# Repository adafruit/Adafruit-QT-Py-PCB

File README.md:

## Adafruit QT Py PCB

<a href="http://www.adafruit.com/products/4600"><br/>
Click here to purchase one from the Adafruit shop</a>

PCB files for the Adafruit QT Py.

Format is EagleCAD schematic and board layout
* https://www.adafruit.com/product/4600

### Description

What a cutie pie! Or is it... a QT Py? This diminutive dev board comes with our favorite lil chip, the SAMD21 (as made famous in our GEMMA M0 and Trinket M0 boards).

This time it comes with our favorite connector - the STEMMA QT, a chainable I2C port that can be used with any of our STEMMA QT sensors and accessories.

OLEDs! Inertial Measurment Units! Sensors a-plenty. All plug-and-play thanks to the innovative chainable design: SparkFun Qwiic-compatible STEMMA QT connectors for the I2C bus so you don't even need to solder! Just plug in a compatible cable and attach it to your MCU of choice, and you’re ready to load up some software and measure some light.

Use any SparkFun Qwiic boards! Seeed Grove I2C boards will also work with this adapter cable.

Pinout and shape is Seeed Xiao compatible, with castellated pads so you can solder it flat to a PCB. In addition to the QT connector, we also added an RGB NeoPixel (with controllable power pin to allow for ultra-low-power usage), and a reset button (great for restarting your program, or entering the bootloader)

Runs Arduino like a dream, and can be used for basic CircuitPython projects. For more advanced usage like datalogging or file storage, solder an SOIC SPI flash chip onto the bottom pads,

    Same size, form-factor, and pin-out as Seeed Xiao
    ATSAMD21E18 32-bit Cortex M0+ - 48 MHz 32 bit processor with 256KB Flash and 32 KB RAM
    Native USB supported by every OS - can be used in Arduino or CircuitPython as USB serial console, MIDI, Keyboard/Mouse HID, even a little disk drive for storing Python scripts.
    Can be used with Arduino IDE or CircuitPython
    Built in RGB NeoPixel LED
    11 GPIO pins:
        True analog output on one I/O pin - can be used to play 10-bit quality audio clips in Arduino (CircuitPython does not have storage for audio clips)
        9 x 12-bit analog inputs (SDA/SCL do not have analog inputs)
        1 x Optional AREF on A1
        9 x PWM outputs (A0 is analog out, A1 is not PWM capable)
        Hardware I2C port with STEMMA QT plug-n-play connector
        Hardware UART
        Hardware SPI
        Hardware I2S
        6 x Capacitive Touch with no additional components required
    3.3V regulator with 600mA peak output
    Optional SOIC-8 SPI Flash chip on bottom
    Reset switch for starting your project code over or entering bootloader mode
    USB Type C connector
    Really really small

### License

Adafruit invests time and resources providing this open source design, please support Adafruit and open-source hardware by purchasing products from [Adafruit](https://www.adafruit.com)!

Designed by Limor Fried/Ladyada for Adafruit Industries.

Creative Commons Attribution/Share-Alike, all text above must be included in any redistribution.
See license.txt for additional details.

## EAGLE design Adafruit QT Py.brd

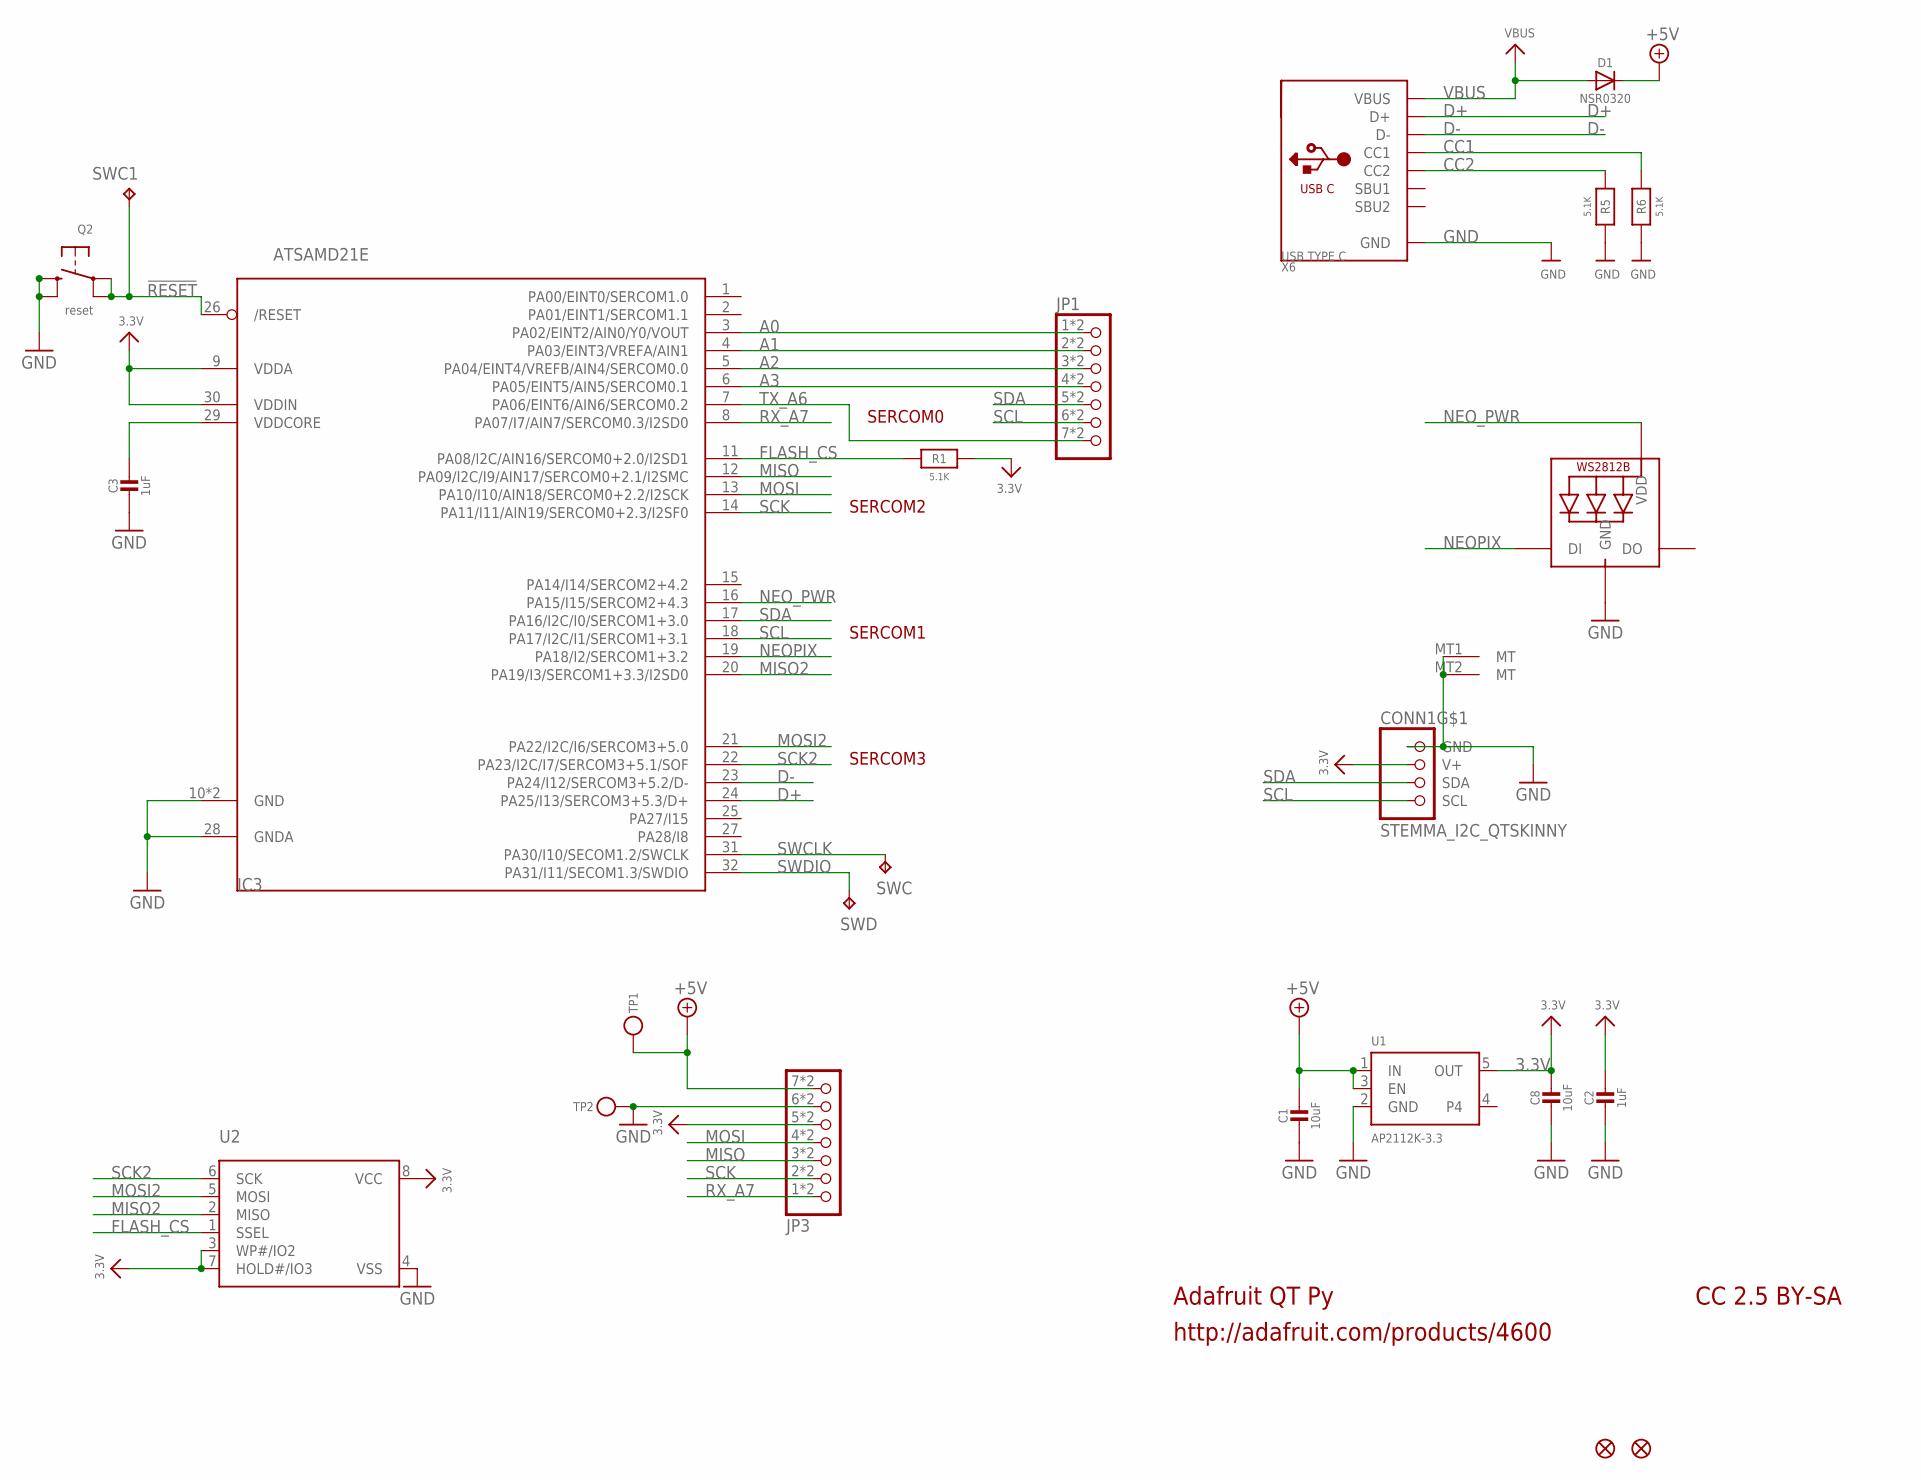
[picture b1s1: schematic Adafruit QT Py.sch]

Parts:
C1, C8: 10uF; _0805MP
C2, C3: 1uF; _0402NO
CONN1: STEMMA_I2C_QTSKINNY; JST_SH4_SKINNY
D1: NSR0320; SOD-323_MINI
IC3: ATSAMD21E; QFN32_5MM
JP1, JP3: HEADER-1X7_CASTEL; 1X07_CASTEL
LED1: WS2812B_SK6805_1515; SK6805_1515
Q2: reset; BTN_KMR2_4.6X2.8
R1, R5, R6: 5.1K; _0402NO
SWC, SWC1: TPB1,27; B1,27
SWD: TPB1,27; B1,27
TP1, TP2: TESTPOINT_1X3; TESTPOINT_RECT_1X3MM
U1: AP2112K-3.3; SOT23-5
U2: SPIFLASH_8PIN; SOIC8_150MIL
U$6, U$8: FIDUCIAL_1MM
X6: USB TYPE C; USB_C_CUSB31-CFM2AX-01-X

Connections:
3.3V: C2.1, C8.1, CONN1.2 (V+), IC3.9 (VDDA), IC3.30 (VDDIN), JP3.5, JP3.5C (5), R1.1, U1.5 (OUT), U2.3 (WP#/IO2), U2.7 (HOLD#/IO3), U2.8 (VCC)
!RESET: IC3.26 (/RESET), Q2.A, Q2.A' (P1), SWC1.TP
+5V: C1.1, D1.C, JP3.7, JP3.7C (7), TP1.P$1, U1.1 (IN), U1.3 (EN)
A0: IC3.3 (PA02/EINT2/AIN0/Y0/VOUT), JP1.1, JP1.1C (1)
A1: IC3.4 (PA03/EINT3/VREFA/AIN1), JP1.2, JP1.2C (2)
A2: IC3.5 (PA04/EINT4/VREFB/AIN4/SERCOM0.0), JP1.3, JP1.3C (3)
A3: IC3.6 (PA05/EINT5/AIN5/SERCOM0.1), JP1.4, JP1.4C (4)
CC1: R6.2, X6.A5 (CC1)
CC2: R5.2, X6.B5 (CC2)
D+: IC3.24 (PA25/I13/SERCOM3+5.3/D+), X6.A6 (D+), X6.B6 (D+)
D-: IC3.23 (PA24/I12/SERCOM3+5.2/D-), X6.A7 (D-), X6.B7 (D-)
FLASH_CS: IC3.11 (PA08/I2C/AIN16/SERCOM0+2.0/I2SD1), R1.2, U2.1 (SSEL)
GND: C1.2, C2.2, C3.2, C8.2, CONN1.1 (GND), CONN1.MT1 (MT), CONN1.MT2 (MT), IC3.10 (GND), IC3.28 (GNDA), IC3.33 (GND), JP3.6, JP3.6C (6), LED1.4 (GND), Q2.B (S), Q2.B' (S1), R5.1, R6.1, TP2.P$1, U1.2 (GND), U2.4 (VSS), X6.A1B12 (GND), X6.B1A12 (GND)
MISO: IC3.12 (PA09/I2C/I9/AIN17/SERCOM0+2.1/I2SMC), JP3.3, JP3.3C (3)
MISO2: IC3.20 (PA19/I3/SERCOM1+3.3/I2SD0), U2.2 (MISO)
MOSI: IC3.13 (PA10/I10/AIN18/SERCOM0+2.2/I2SCK), JP3.4, JP3.4C (4)
MOSI2: IC3.21 (PA22/I2C/I6/SERCOM3+5.0), U2.5 (MOSI)
NEOPIX: IC3.19 (PA18/I2/SERCOM1+3.2), LED1.1 (DI)
NEO_PWR: IC3.16 (PA15/I15/SERCOM2+4.3), LED1.2 (VDD)
RX_A7: IC3.8 (PA07/I7/AIN7/SERCOM0.3/I2SD0), JP3.1, JP3.1C (1)
SCK: IC3.14 (PA11/I11/AIN19/SERCOM0+2.3/I2SF0), JP3.2, JP3.2C (2)
SCK2: IC3.22 (PA23/I2C/I7/SERCOM3+5.1/SOF), U2.6 (SCK)
SCL: CONN1.4 (SCL), IC3.18 (PA17/I2C/I1/SERCOM1+3.1), JP1.6, JP1.6C (6)
SDA: CONN1.3 (SDA), IC3.17 (PA16/I2C/I0/SERCOM1+3.0), JP1.5, JP1.5C (5)
SWCLK: IC3.31 (PA30/I10/SECOM1.2/SWCLK), SWC.TP
SWDIO: IC3.32 (PA31/I11/SECOM1.3/SWDIO), SWD.TP
TX_A6: IC3.7 (PA06/EINT6/AIN6/SERCOM0.2), JP1.7, JP1.7C (7)
VBUS: D1.A, X6.A4B9 (VBUS), X6.B4A9 (VBUS)
VDDCORE: C3.1, IC3.29 (VDDCORE)

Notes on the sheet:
Adafruit QT Py
http://adafruit.com/products/4600
CC 2.5 BY-SA
SERCOM0
SERCOM1
SERCOM2
SERCOM3

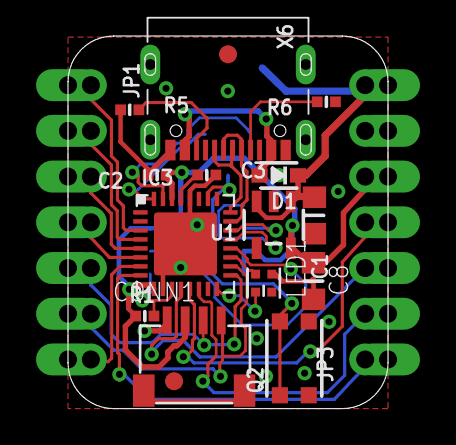
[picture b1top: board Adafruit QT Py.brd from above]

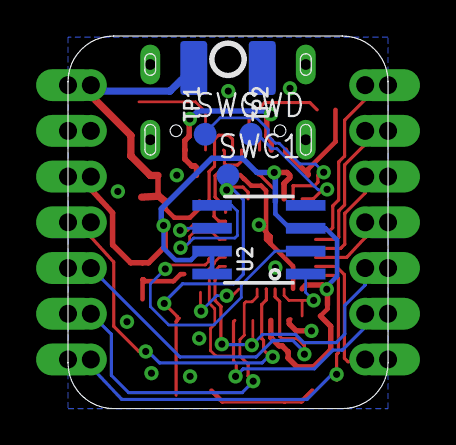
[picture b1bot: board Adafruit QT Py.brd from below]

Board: 2 copper layers, 17.8 x 20.7 mm, 27 parts (8 on the bottom side), 29 nets.

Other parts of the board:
U$11: QTPY_BOT
U$12: PCBFEAT-REV-040
U$13: QTPY_TOP

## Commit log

2020-09-28 Adding board files.
2020-10-06 Update board files.
2021-05-18 Add pinout PDF

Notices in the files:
parts and their libraries:
microbuilder: This work is placed in the public domain, and may be freely used for commercial and non-commercial work with the following conditions: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
